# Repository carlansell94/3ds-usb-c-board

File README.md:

A small board designed to replace the proprietary Nintendo 3DS dock charging port with a USB type C port. This board is suitable for official Nintendo 3DS, New 3DS, 3DS XL and New 3DS XL docks, which all contain the same small PCB on the inside.

Features:
* Includes pads for 5.1k&#937; resistors, to allow the use of 'smart' chargers.
* Board is a near drop-in replacement for the original.
* Pads on the + output allow the addition of a switch - bridge these pads with solder if you're not using one. Alternatively, use the switchless version of the board.

Minor alterations to the dock are required, due to the USB type C port being physically larger than the original. More details on the required sanding can be found [on my blog](https://qubitsandbytes.co.uk/convert-a-nintendo-3ds-dock-to-usb-c/).

Included in this repository are the KiCAD files for this design. If you're only interested in having the board manufactured, gerbers are available under 'releases'.

Parts List:
* 1x 16 pin USB type C port
* 2x 0603 5.1k&#937; resistors (optional)
* 1x 2 pin switch (optional)

A tri-wing screwdriver is required, to remove the dock base.

When having the board manufactured, ensure they offer a 0.8mm board thickness - I used OSH Park for mine.

## Images
KiCAD render:

## KiCAD
The files in this project were created using KiCAD 7. Older versions of KiCAD will be unable to open these files.

In addition, the USB Type C port pictured in the 3D render can be found [over here](https://github.com/ai03-2725/Type-C.pretty) - the file you're looking for is 'HRO TYPE-C-31-M-12.step'. It's not required, unless you want to see the part populated using the 3D viewer.

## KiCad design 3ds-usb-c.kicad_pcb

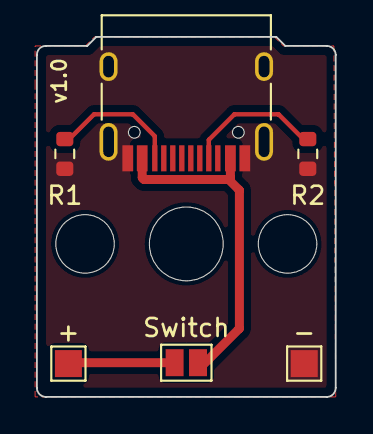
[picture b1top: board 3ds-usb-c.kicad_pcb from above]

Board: 2 copper layers, 16.6 x 20.0 mm, 6 parts (0 on the bottom side), 5 nets.

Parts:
+: +; TestPoint_Pad_1.5x1.5mm
-: -; TestPoint_Pad_1.5x1.5mm
J1: USB_C_Receptacle; USB_C_Receptacle_HRO_TYPE-C-31-M-12
R1, R2: 5.1k; R_0603_1608Metric
Switch: SolderJumper-2_P1.3mm_Open_Pad1.0x1.5mm

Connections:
GND: -.1, J1.A1 (GND), J1.A12 (GND), J1.B1 (GND), J1.B12 (GND), J1.S1 (SHIELD), R1.2, R2.2
unnamed: J1.A4 (VBUS), J1.A9 (VBUS), J1.B4 (VBUS), J1.B9 (VBUS), Switch.1
unnamed: J1.A5 (CC1), R2.1
unnamed: J1.B5 (CC2), R1.1
unnamed: +.1, Switch.2

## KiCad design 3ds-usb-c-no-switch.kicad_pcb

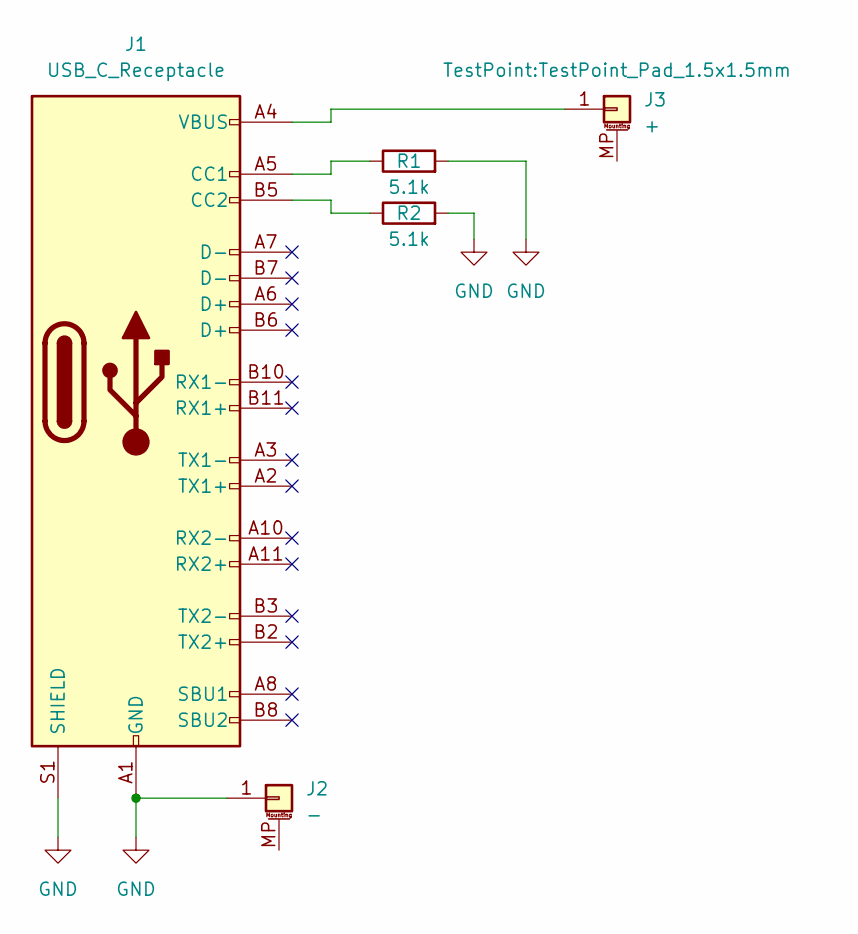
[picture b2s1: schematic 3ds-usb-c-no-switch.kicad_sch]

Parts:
J1: USB_C_Receptacle; USB_C_Receptacle_HRO_TYPE-C-31-M-12
J2: -; TestPoint_Pad_1.5x1.5mm
J3: +; TestPoint_Pad_1.5x1.5mm
R1, R2: 5.1k; R_0603_1608Metric

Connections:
GND: J1.A1 (GND), J1.A12 (GND), J1.B1 (GND), J1.B12 (GND), J1.S1 (SHIELD), J2.1, R1.2, R2.2
unnamed: J1.A5 (CC1), R1.1
unnamed: J1.B5 (CC2), R2.1
unnamed: J1.A4 (VBUS), J1.A9 (VBUS), J1.B4 (VBUS), J1.B9 (VBUS), J3.1

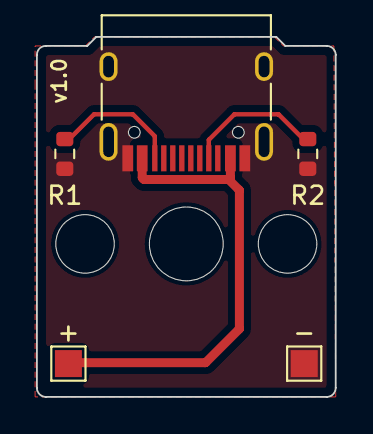
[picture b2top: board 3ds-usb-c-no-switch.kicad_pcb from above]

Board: 2 copper layers, 16.6 x 20.0 mm, 5 parts (0 on the bottom side), 4 nets.
